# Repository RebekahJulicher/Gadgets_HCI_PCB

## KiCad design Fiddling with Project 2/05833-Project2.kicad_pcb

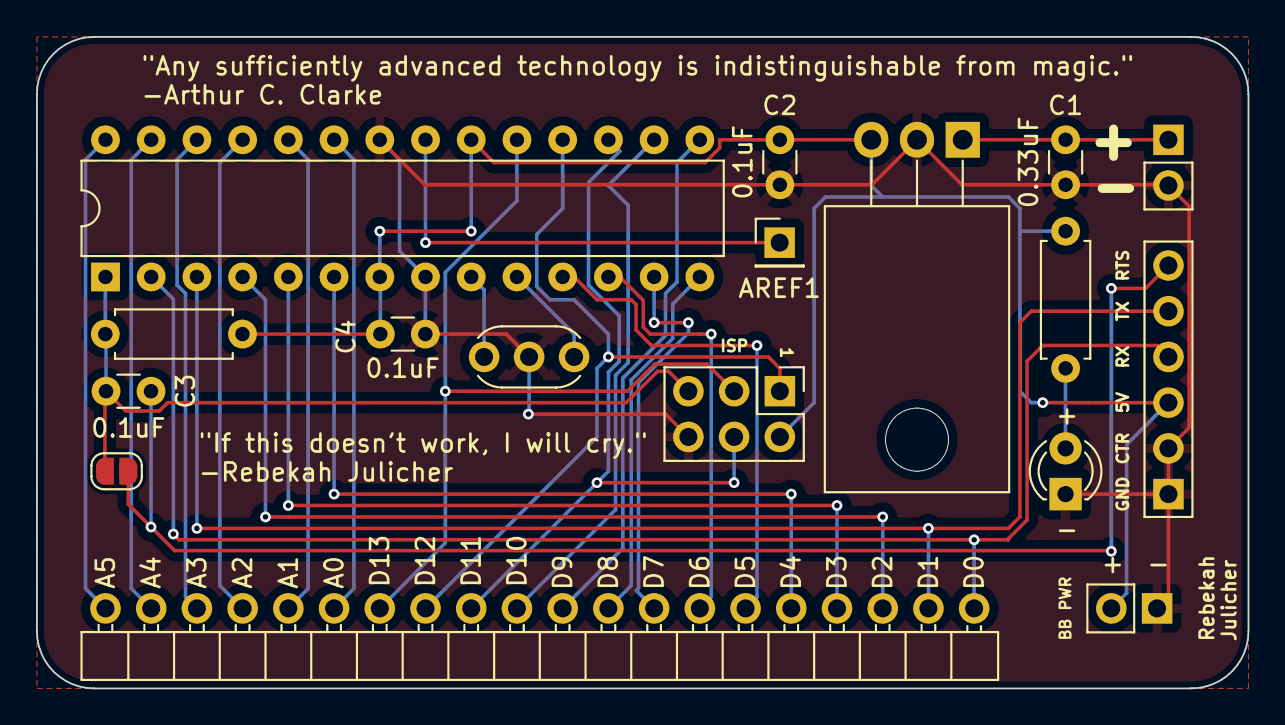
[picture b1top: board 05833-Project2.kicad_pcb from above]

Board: 2 copper layers, 67.3 x 36.2 mm, 17 parts (0 on the bottom side), 29 nets.

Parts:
AREF1: AREF; PinHeader_1x01_P2.54mm_Vertical
BT1: 9V Clip; Battery_SnapConnector
C1: 0.33uF; C_Disc_D3.0mm_W1.6mm_P2.50mm
C2, C3, C4: 0.1uF; C_Disc_D3.0mm_W1.6mm_P2.50mm
D1: LED; LED_D3.0mm
J1: BB Power; BB_PowerRails
J2: FTDI; FTDI_1x06_P2.54mm_Vertical
J3: ISP; PinHeader_2x03_P2.54mm_Vertical
J4: GPIO; ArduinoGPIO_1x20_P2.54mm_Horizontal
JP1: SolderJumper_2_Open; SolderJumper-2_P1.3mm_Open_RoundedPad1.0x1.5mm
R1: 10K; R_Axial_QuarterWatt_Horizontal
R2: R; R_Axial_DIN0207_L6.3mm_D2.5mm_P7.62mm_Horizontal
U1: LM7805; TO-220-3_Horizontal_TabDown
U2: ATmega328-P; DIP-28_W7.62mm
Y1: 16MHz Resonator; Resonator-3Pin_W6.0mm_H3.0mm

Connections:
+5V: C2.1, C4.2, J1.2, J2.3, J3.2, R1.1, R2.1, U1.3 (VO), U2.7 (VCC), U2.20 (AVCC)
+9V: BT1.1 (+), C1.1, U1.1 (VI)
/A0: J4.15, U2.23 (PC0)
/A1: J4.16, U2.24 (PC1)
/A2: J4.17, U2.25 (PC2)
/A3: J4.18, U2.26 (PC3)
/A4: J4.19, U2.27 (PC4)
/A5: J4.20, U2.28 (PC5)
/D0: J2.4, J4.1, U2.2 (PD0)
/D1: J2.5, J4.2, U2.3 (PD1)
/D2: J4.3, U2.4 (PD2)
/D3: J4.4, U2.5 (PD3)
/D4: J4.5, U2.6 (PD4)
/D5: J4.6, U2.11 (PD5)
/D6: J4.7, U2.12 (PD6)
/D7: J4.8, U2.13 (PD7)
/D8: J4.9, U2.14 (PB0)
/D9: J4.10, U2.15 (PB1)
/D10: J4.11, U2.16 (PB2)
/D11: J3.4, J4.12, U2.17 (PB3)
/D12: J3.1, J4.13, U2.18 (PB4)
/D13: J3.3, J4.14, U2.19 (PB5)
/DTR: C3.2, J2.6, JP1.2 (B)
/RESET: C3.1, J3.5, JP1.1 (A), R1.2, U2.1 (~RESET/PC6)
GND: BT1.2 (-), C1.2, C2.2, C4.1, D1.1 (K), J1.1, J2.1, J2.2, J3.6, U1.2 (GND), U2.8 (GND), U2.22 (GND), Y1.2
unnamed: AREF1.1, U2.21 (AREF)
unnamed: D1.2 (A), R2.2
unnamed: U2.9 (XTAL1/PB6), Y1.3
unnamed: U2.10 (XTAL2/PB7), Y1.1

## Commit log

2024-03-28 P2 File Commit
2024-03-28 Updates to the edge cuts
2024-03-28 Revamped
2024-03-28 solder jumper
2024-03-28 Final touches
2024-03-29 Finished
2024-04-01 Complete and ordered
